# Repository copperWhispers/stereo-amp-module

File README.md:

# STEREO AMP MODULE

An open-source stereo class-D amplifier board built around the TI TPA3116D2. Full KiCad source, gerbers, and a BOM.
Link to TPA3116D2 Part: https://www.ti.com/lit/ds/symlink/tpa3118d2.pdf?ts=1788008862639&ref_url=https%253A%252F%252Fwww.ti.com%252Fproduct%252FTPA3118D2
This is an interesting part with many different configurations which can handle 4 ohms and 8 ohms Stereo Speakers at various Power ratings:

**Here is an image of the PCB I designed for it:**

---

## What it is

| | |
|---|---|
| **Amplifier** | TPA3116D2DADR — class-D, stereo, BTL |
| **Configuration** | Master mode, 26 dB gain, differential inputs |
| **Supply** | 4.5–20 V (built and tested at 12 V) Could go to 26V with different caps.|
| **Output** | ~18 W into 4 Ω, limited by the 12 V rail |
| **Idle current** | ~50 mA at 12 V |
| **Assembly** | Hand-solderable — 0603 passives, HTSSOP-32|

An interactive BOM is included at [`docs/ibom.html`](docs/ibom.html) — open it in a browser and it highlights each part on the board as you work through the build.

---

## Build it

BOM: Open docs/ibom.html in a browser.

**Boards:** order `production/gerbers.zip` from JLCPCB or PCBWay, or build the boards yourself.

**Schematic:** [`docs/schematic.pdf`](docs/schematic.pdf) · **Board:** [`docs/pcb.pdf`](docs/pcb.pdf)

## Errata — v1 needs two wire links

As the board is single layer as I am building it using a UV, photosensitive film and copper clad board method, thus external connections have to be made via wires, I have placed pads on the layout to make the soldering process easier:

**Wire link between these pads:**

**Solder bridge across these legs:**

---

## Extras

**GAIN**

Going in, I expected to set the gain to whatever the maths called for, pick a resistor ratio, get that gain. The TPA3116D2 doesn't work that way. It offers four fixed settings: 20, 26, 32 and 36 dB selected by a voltage divider on the GAIN/SLV pin. The setting latches at power-up and can't be changed while running. 
I will thus be modulating the volume via a later preamp module that will also serve as an inputs mixer, I will probably add a couple of other fun features on there too, and it will allow me to protect the input of the audio amplifier by ensuring that signals get attenuating to the right scale before going in.

This board ended up at **26 dB** (20 kΩ to GND, 100 kΩ to GVDD). Which if we use the equation  dB = 20 * Log(Gain)  then rearrange for Gain ->  Gain = 10^(dB/20) we get Gain = 19.95.

However as I show in the video there are many other settings that you can configure this gain to and this can be achieved simply by changing the GAIN/SLV resistor values:

**BTL vs SLV**

**Speakers Safety:** 

the speakers are never at risk. On a 12 V rail the maximum output is about 18 W into 4 Ω, and the speakers are rated 20 W. The supply voltage is the protection, the amplifier physically cannot deliver enough power to damage them, whatever you do with the volume knob.

---

## Video

[https://youtu.be/IWhPQ7ZQIiU](https://youtu.be/IWhPQ7ZQliU?si=qsnklUcxvsyva8gy)

---

Built one? Open an issue with a photo — I'd like to see it.

New board every month: [copperWhispers](https://copperwhispers.com)

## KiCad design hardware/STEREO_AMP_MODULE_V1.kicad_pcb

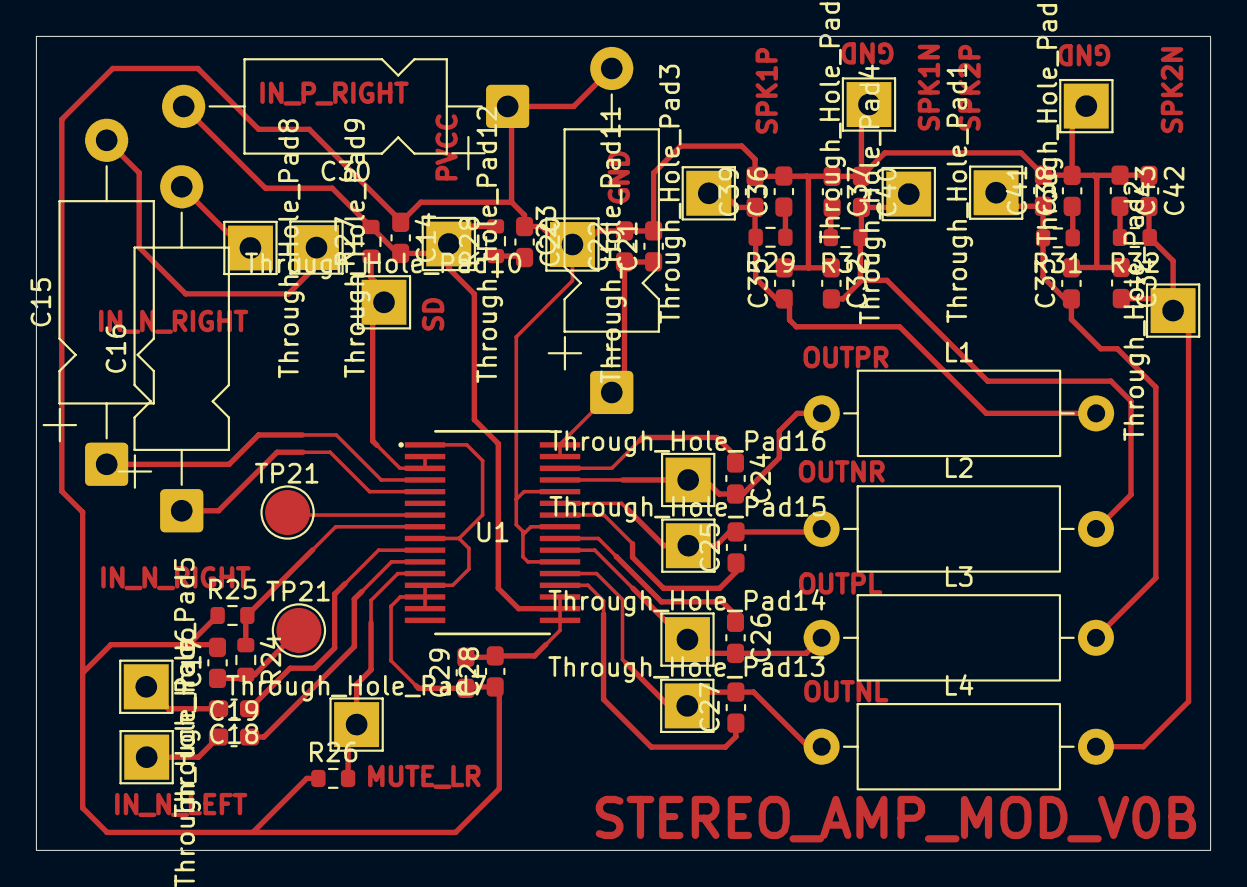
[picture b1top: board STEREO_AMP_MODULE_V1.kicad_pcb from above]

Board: 2 copper layers, 65.2 x 45.2 mm, 63 parts (0 on the bottom side), 32 nets.

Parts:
C14, C36, C37, C38, C43: 10n; C_0603_1608Metric_Pad1.08x0.95mm_HandSolder
C15, C16: 10u; CP_Axial_L11.0mm_D5.0mm_P18.00mm_Horizontal
C17, C18, C19: 1u; C_0603_1608Metric_Pad1.08x0.95mm_HandSolder
C20, C22, C29: 100n; C_0603_1608Metric_Pad1.08x0.95mm_HandSolder
C21, C28, C39, C40, C41, C42: 1n; C_0603_1608Metric_Pad1.08x0.95mm_HandSolder
C23, C30: 220u; CP_Axial_L11.0mm_D5.0mm_P18.00mm_Horizontal
C24, C25, C26, C27: 220n; C_0603_1608Metric_Pad1.08x0.95mm_HandSolder
C32, C33, C34, C35: 1.4u; C_0603_1608Metric_Pad1.08x0.95mm_HandSolder
L1, L2, L3, L4: 11u; L_Axial_L11.0mm_D4.5mm_P15.24mm_Horizontal_Fastron_MECC
R24: 20k; R_0603_1608Metric
R25, R26, R27: 100k; R_0603_1608Metric
R28, R29, R30, R31, R32: 3.3; R_0603_1608Metric
TP21, TP21#2: TestPoint; TestPoint_Pad_D2.5mm
Through_Hole_Pad1, Through_Hole_Pad2, Through_Hole_Pad3, Through_Hole_Pad4, Through_Hole_Pad5, Through_Hole_Pad6, Through_Hole_Pad7, Through_Hole_Pad8, Through_Hole_Pad9, Through_Hole_Pad10, Through_Hole_Pad11, Through_Hole_Pad12, Through_Hole_Pad13, Through_Hole_Pad14, Through_Hole_Pad15, Through_Hole_Pad16, Through_Hole_Pad21, Through_Hole_Pad22: TestPoint_THTPad_2.5x2.5mm_Drill1.2mm
U1: TPA3116D2DADR; DAD0032A_L

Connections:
/OUTNL_PWR: C27.2, L4.1, Through_Hole_Pad13.1, U1.21 (OUTNL)
/OUTNR_PWR: C25.2, L2.1, Through_Hole_Pad15.1, U1.27 (OUTNR)
/OUTPL_PWR: C26.2, L3.1, Through_Hole_Pad14.1, U1.23 (OUTPL)
/OUTPR_PWR: C24.2, L1.1, Through_Hole_Pad16.1, U1.29 (OUTPR)
GND_PWR: C14.1, C17.2, C20.1, C21.2, C22.2, C23.2, C28.1, C29.1, C30.1, C32.1, C33.2, C34.1, C35.2, C36.2, C37.1, C38.2, C39.2, C40.1, C41.2, C42.1, C43.1, R25.1, R26.1, Through_Hole_Pad11.1, Through_Hole_Pad21.1, Through_Hole_Pad22.1, U1.1 (MODSEL), U1.9 (GND), U1.13 (AM2), U1.14 (AM1), U1.15 (AM0), U1.22 (GND), U1.25 (GND), U1.28 (GND)
IN_N_LEFT: C19.1, Through_Hole_Pad6.1
IN_N_RIGHT: C16.2, Through_Hole_Pad8.1
IN_P_LEFT: C18.2, Through_Hole_Pad5.1
IN_P_RIGHT: C15.2, Through_Hole_Pad9.1
MUTE_LR: R26.2, Through_Hole_Pad7.1, U1.12 (MUTE)
unnamed: C20.2, R28.1
unnamed: C21.1, C22.1, C23.1, U1.31 (PVCC), U1.32 (PVCC)
unnamed: C36.1, R29.1
unnamed: C37.2, R30.2
unnamed: C38.1, R31.1
unnamed: C43.2, R32.2
unnamed: C27.1, U1.20 (BSNL)
unnamed: C25.1, U1.26 (BSNR)
unnamed: C26.1, U1.24 (BSPL)
unnamed: C24.1, U1.30 (BSPR)
unnamed: R24.1, R25.2, U1.8 (GAIN_SLV)
unnamed: C17.1, R24.2, TP21.1 (1_1), TP21#2.1 (1_1), U1.6 (PLIMIT), U1.7 (GVDD)
unnamed: C19.2, U1.11 (LINN)
unnamed: C18.1, U1.10 (LINP)
unnamed: C16.1, U1.5 (RINN)
unnamed: C15.1, U1.4 (RINP)
PVCC_PWR: C14.2, C28.2, C29.2, C30.2, R27.2, R28.2, Through_Hole_Pad12.1, U1.17 (AVCC), U1.18 (PVCC), U1.19 (PVCC)
SPK1_NEG_PWR: C32.2, C40.2, L2.2, R30.1, Through_Hole_Pad4.1
SPK1_POS_PWR: C35.1, C39.1, L1.2, R29.2, Through_Hole_Pad3.1
SPK2_NEG_PWR: C34.2, C42.2, L4.2, R32.1, Through_Hole_Pad2.1
SPK2_POS_PWR: C33.1, C41.1, L3.2, R31.2, Through_Hole_Pad1.1
/SD_LR: R27.1, Through_Hole_Pad10.1, U1.2 (SDZ), U1.3 (FAULTZ)

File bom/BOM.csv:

"Refs","Value","Footprint","Qty","DNP"
"C14","10n","Capacitor_SMD:C_0603_1608Metric_Pad1.08x0.95mm_HandSolder","1",""
"C15","10u","Capacitor_THT:CP_Axial_L11.0mm_D5.0mm_P18.00mm_Horizontal","1",""
"C16","10u","Capacitor_THT:CP_Axial_L11.0mm_D5.0mm_P18.00mm_Horizontal","1",""
"C17","1u","Capacitor_SMD:C_0603_1608Metric_Pad1.08x0.95mm_HandSolder","1",""
"C18","1u","Capacitor_SMD:C_0603_1608Metric_Pad1.08x0.95mm_HandSolder","1",""
"C19","1u","Capacitor_SMD:C_0603_1608Metric_Pad1.08x0.95mm_HandSolder","1",""
"C20","100n","Capacitor_SMD:C_0603_1608Metric_Pad1.08x0.95mm_HandSolder","1",""
"C21","1n","Capacitor_SMD:C_0603_1608Metric_Pad1.08x0.95mm_HandSolder","1",""
"C22","100n","Capacitor_SMD:C_0603_1608Metric_Pad1.08x0.95mm_HandSolder","1",""
"C23","220u","Capacitor_THT:CP_Axial_L11.0mm_D5.0mm_P18.00mm_Horizontal","1",""
"C24","220n","Capacitor_SMD:C_0603_1608Metric_Pad1.08x0.95mm_HandSolder","1",""
"C25","220n","Capacitor_SMD:C_0603_1608Metric_Pad1.08x0.95mm_HandSolder","1",""
"C26","220n","Capacitor_SMD:C_0603_1608Metric_Pad1.08x0.95mm_HandSolder","1",""
"C27","220n","Capacitor_SMD:C_0603_1608Metric_Pad1.08x0.95mm_HandSolder","1",""
"C28","1n","Capacitor_SMD:C_0603_1608Metric_Pad1.08x0.95mm_HandSolder","1",""
"C29","100n","Capacitor_SMD:C_0603_1608Metric_Pad1.08x0.95mm_HandSolder","1",""
"C30","220u","Capacitor_THT:CP_Axial_L11.0mm_D5.0mm_P18.00mm_Horizontal","1",""
"C32","1.4u","Capacitor_SMD:C_0603_1608Metric_Pad1.08x0.95mm_HandSolder","1",""
"C33","1.4u","Capacitor_SMD:C_0603_1608Metric_Pad1.08x0.95mm_HandSolder","1",""
"C34","1.4u","Capacitor_SMD:C_0603_1608Metric_Pad1.08x0.95mm_HandSolder","1",""
"C35","1.4u","Capacitor_SMD:C_0603_1608Metric_Pad1.08x0.95mm_HandSolder","1",""
"C36","10n","Capacitor_SMD:C_0603_1608Metric_Pad1.08x0.95mm_HandSolder","1",""
"C37","10n","Capacitor_SMD:C_0603_1608Metric_Pad1.08x0.95mm_HandSolder","1",""
"C38","10n","Capacitor_SMD:C_0603_1608Metric_Pad1.08x0.95mm_HandSolder","1",""
"C39","1n","Capacitor_SMD:C_0603_1608Metric_Pad1.08x0.95mm_HandSolder","1",""
"C40","1n","Capacitor_SMD:C_0603_1608Metric_Pad1.08x0.95mm_HandSolder","1",""
"C41","1n","Capacitor_SMD:C_0603_1608Metric_Pad1.08x0.95mm_HandSolder","1",""
"C42","1n","Capacitor_SMD:C_0603_1608Metric_Pad1.08x0.95mm_HandSolder","1",""
"C43","10n","Capacitor_SMD:C_0603_1608Metric_Pad1.08x0.95mm_HandSolder","1",""
"J1","SpeakON_NL2","","1",""
"J2","SpeakON_NL2","","1",""
"L1","11u","Inductor_THT:L_Axial_L11.0mm_D4.5mm_P15.24mm_Horizontal_Fastron_MECC","1",""
"L2","11u","Inductor_THT:L_Axial_L11.0mm_D4.5mm_P15.24mm_Horizontal_Fastron_MECC","1",""
"L3","11u","Inductor_THT:L_Axial_L11.0mm_D4.5mm_P15.24mm_Horizontal_Fastron_MECC","1",""
"L4","11u","Inductor_THT:L_Axial_L11.0mm_D4.5mm_P15.24mm_Horizontal_Fastron_MECC","1",""
"R24","20k","Resistor_SMD:R_0603_1608Metric","1",""
"R25","100k","Resistor_SMD:R_0603_1608Metric","1",""
"R26","100k","Resistor_SMD:R_0603_1608Metric","1",""
"R27","100k","Resistor_SMD:R_0603_1608Metric","1",""
"R28","3.3","Resistor_SMD:R_0603_1608Metric","1",""
"R29","3.3","Resistor_SMD:R_0603_1608Metric","1",""
"R30","3.3","Resistor_SMD:R_0603_1608Metric","1",""
"R31","3.3","Resistor_SMD:R_0603_1608Metric","1",""
"R32","3.3","Resistor_SMD:R_0603_1608Metric","1",""
"Through_Hole_Pad1","","TestPoint:TestPoint_THTPad_2.5x2.5mm_Drill1.2mm","1",""
"Through_Hole_Pad2","","TestPoint:TestPoint_THTPad_2.5x2.5mm_Drill1.2mm","1",""
"Through_Hole_Pad3","","TestPoint:TestPoint_THTPad_2.5x2.5mm_Drill1.2mm","1",""
"Through_Hole_Pad4","","TestPoint:TestPoint_THTPad_2.5x2.5mm_Drill1.2mm","1",""
"Through_Hole_Pad5","","TestPoint:TestPoint_THTPad_2.5x2.5mm_Drill1.2mm","1",""
"Through_Hole_Pad6","","TestPoint:TestPoint_THTPad_2.5x2.5mm_Drill1.2mm","1",""
"Through_Hole_Pad7","","TestPoint:TestPoint_THTPad_2.5x2.5mm_Drill1.2mm","1",""
"Through_Hole_Pad8","","TestPoint:TestPoint_THTPad_2.5x2.5mm_Drill1.2mm","1",""
"Through_Hole_Pad9","","TestPoint:TestPoint_THTPad_2.5x2.5mm_Drill1.2mm","1",""
"Through_Hole_Pad10","","TestPoint:TestPoint_THTPad_2.5x2.5mm_Drill1.2mm","1",""
"Through_Hole_Pad11","","TestPoint:TestPoint_THTPad_2.5x2.5mm_Drill1.2mm","1",""
"Through_Hole_Pad12","","TestPoint:TestPoint_THTPad_2.5x2.5mm_Drill1.2mm","1",""
"Through_Hole_Pad13","","TestPoint:TestPoint_THTPad_2.5x2.5mm_Drill1.2mm","1",""
"Through_Hole_Pad14","","TestPoint:TestPoint_THTPad_2.5x2.5mm_Drill1.2mm","1",""
"Through_Hole_Pad15","","TestPoint:TestPoint_THTPad_2.5x2.5mm_Drill1.2mm","1",""
"Through_Hole_Pad16","","TestPoint:TestPoint_THTPad_2.5x2.5mm_Drill1.2mm","1",""
"Through_Hole_Pad17","","TestPoint:TestPoint_THTPad_2.5x2.5mm_Drill1.2mm","1",""
"Through_Hole_Pad18","","TestPoint:TestPoint_THTPad_2.5x2.5mm_Drill1.2mm","1",""
"Through_Hole_Pad19","","TestPoint:TestPoint_THTPad_2.5x2.5mm_Drill1.2mm","1",""
"Through_Hole_Pad20","","TestPoint:TestPoint_THTPad_2.5x2.5mm_Drill1.2mm","1",""
"Through_Hole_Pad21","","TestPoint:TestPoint_THTPad_2.5x2.5mm_Drill1.2mm","1",""
"Through_Hole_Pad22","","TestPoint:TestPoint_THTPad_2.5x2.5mm_Drill1.2mm","1",""
"U1","TPA3116D2DADR","TPA3116D2DADR:DAD0032A_L","1",""
